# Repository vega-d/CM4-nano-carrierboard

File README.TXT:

These files have been created in prerelease version 6 of KiCAD. If Version 6 isn't released yet then to use them you will need to download a nightly build of KiCAD. NB Nightly builds my have issues so please check the issue tracker. 

Some of the 3d models need to be downloaded form the following places and put into the CM4IO.3shapes directory some models are approximations.

https://datasheets.raspberrypi.org/cm4/CM4-step.zip
https://www.amphenol-icc.com/pci-express-1001878311200tlf.html
https://www.te.com/global-en/product-171826-4.html
https://www.molex.com/molex/products/part-detail/memory_card_socket/5033981892

The models provided in the 3dmodels directory are from various manufacturers including Diodes, Hirose, MTCONN,Toby, TRXCOM. Terms and conditions for the use of the models remain with the original manufacture.

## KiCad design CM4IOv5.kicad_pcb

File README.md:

# CM4-nano-carrierboard
 A simplified carrier board for RPI CM4 module featuring reduced footprint.

- Uses 5V barrel plug charger for power.
- Has one full size HDMI port.
- has 2 usb-2.0 ports.
- sd card support.
- built-in gigabit ethernet.

SIZE: 80mm x 90mm.

- grounded infill
- use kicad 5.99 or newer.

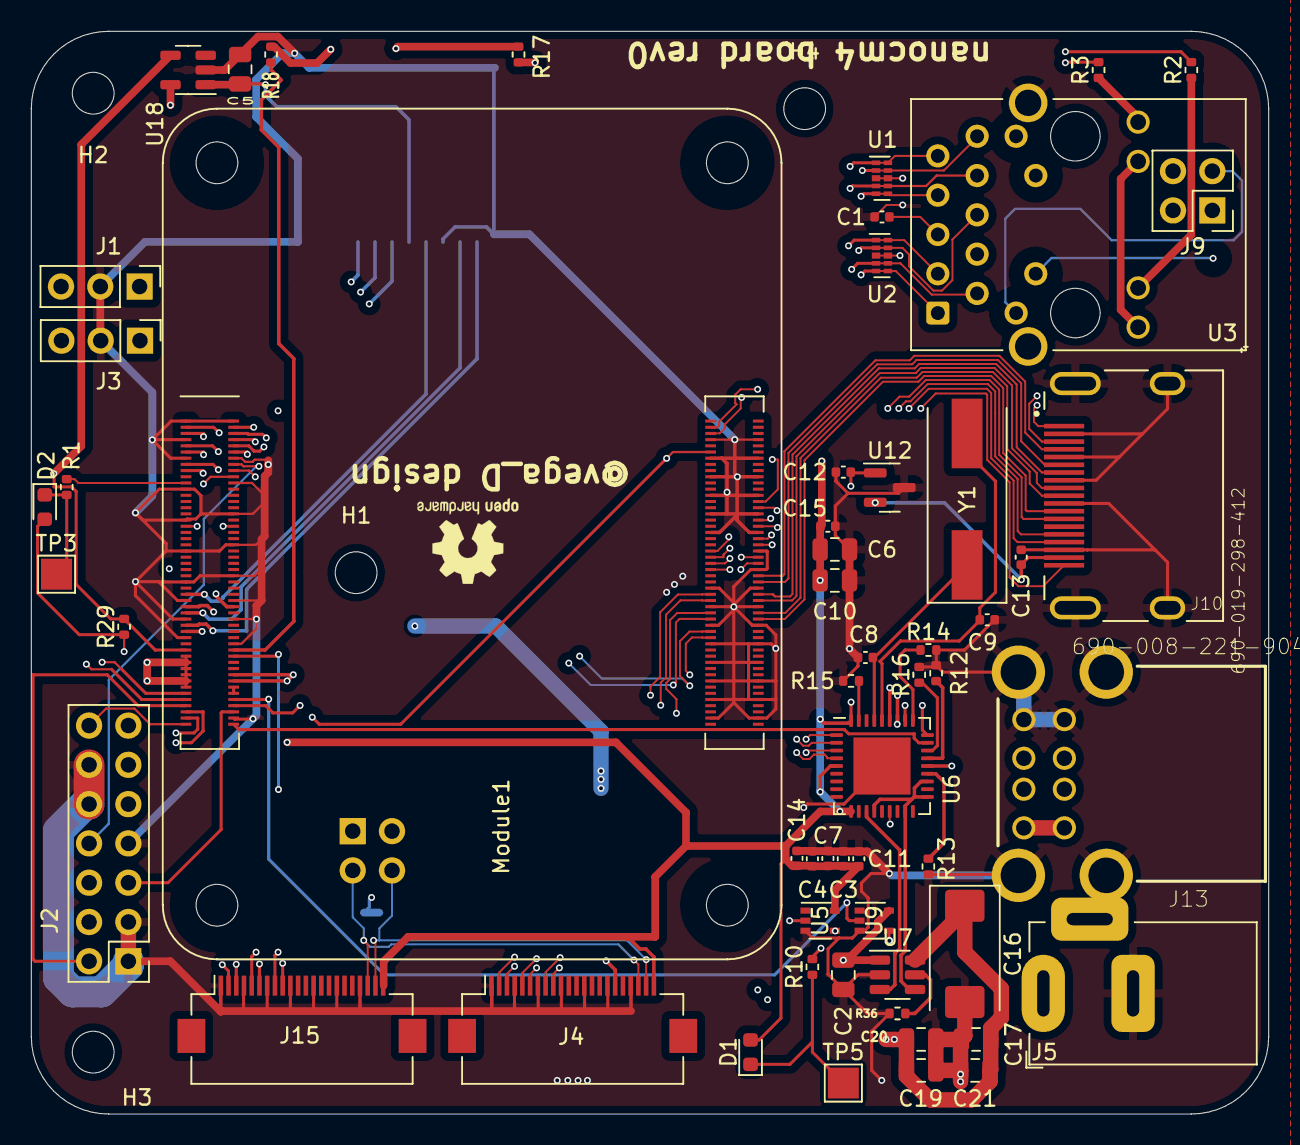
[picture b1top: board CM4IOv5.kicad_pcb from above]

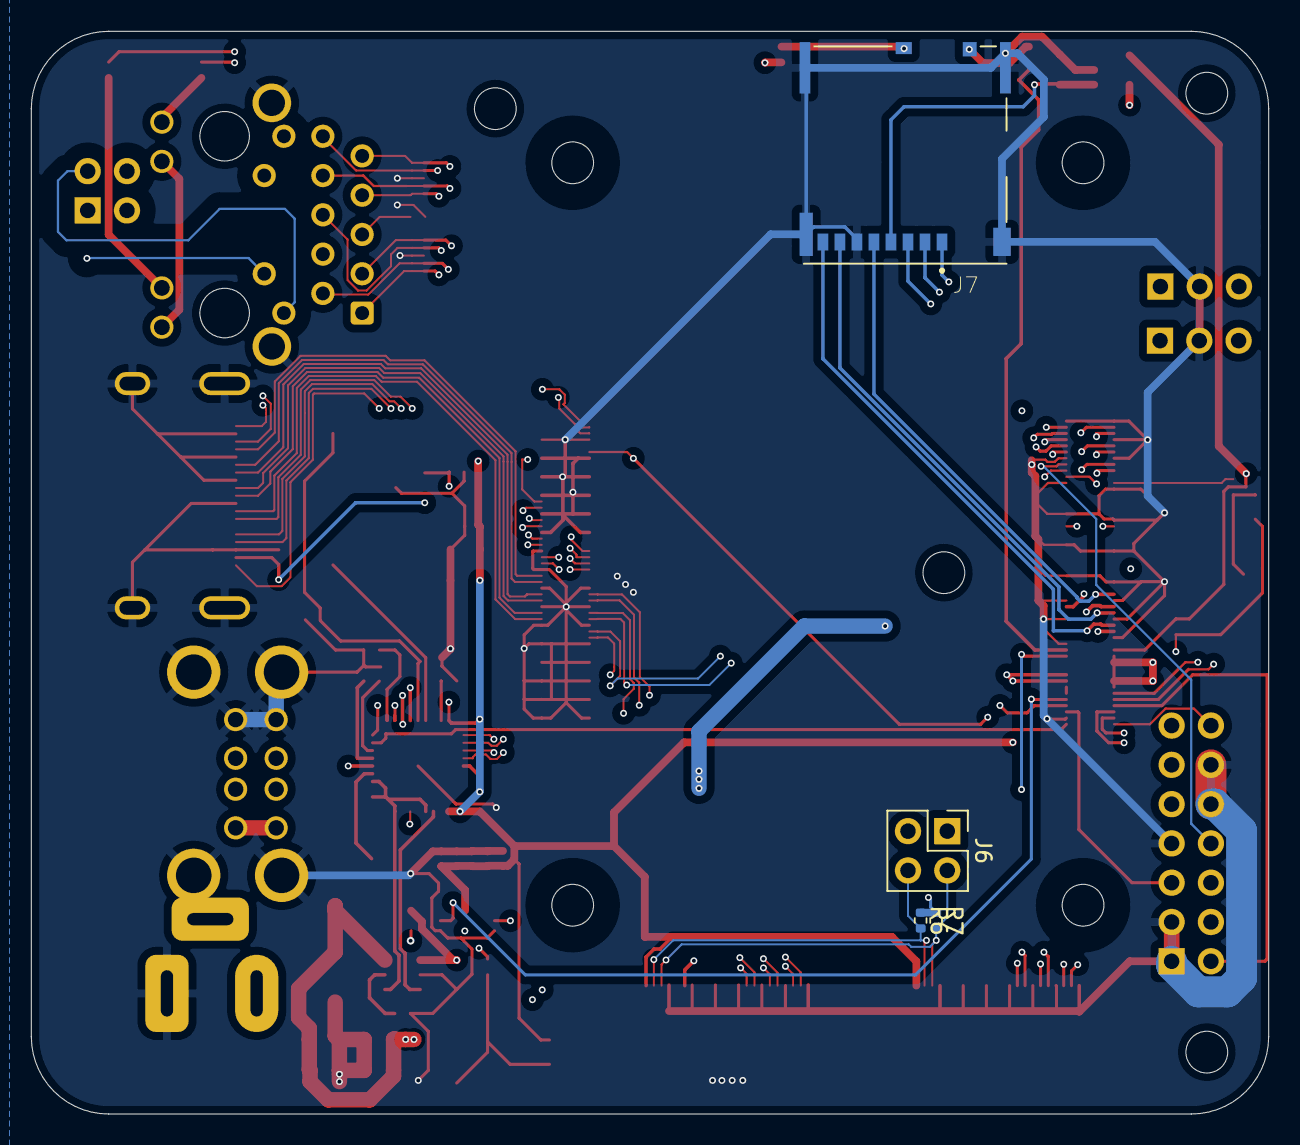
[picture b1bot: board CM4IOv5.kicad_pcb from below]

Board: 4 copper layers, 80.0 x 70.0 mm, 65 parts (4 on the bottom side), 98 nets.

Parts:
C1, C3, C4, C7, C11, C12, C13, C14, C15: 100n; C_0402_1005Metric
C2, C5, C6, C10, C17, C19, C20, C21: 10u; C_0805_2012Metric
C8, C9: 27pF; C_0402_1005Metric
C16: 100uF; CP_EIA-7343-31_Kemet-D
D1: LED Red; LED_0603_1608Metric
D2: LED Green; LED_0603_1608Metric
H1, H2, H3, H4: MountingHole; MountingHole_2.7mm_M2.5
J1, J3: Conn_01x03; PinHeader_1x03_P2.54mm_Vertical
J2: Conn_02x07_Odd_Even; PinHeader_2x07_P2.54mm_Vertical
J4, J15: Conn_01x22_Female; Hirose_FH12-22S-0.5SH_1x22-1MP_P0.50mm_Horizontal
J5: Barrel_Jack; BarrelJack_Horizontal
J6, J9: THD-02-R; PinHeader_2x02_P2.54mm_Vertical
J7: Micro_SD_Card_Det; SDCARD_MOLEX_503398-1892
J10: 690-019-298-412; EDAC 690-019-298-412
J13: 690-008-221-904; MOLEX_USB_67298-4090
Module1: ComputeModule4; Raspberry-Pi-4-Compute-Module
R1, R10: 1k; R_0402_1005Metric
R2, R3: 470R; R_0402_1005Metric
R6, R7: 2.2K 1%; R_0402_1005Metric
R12, R13, R14, R16: 36K 1%; R_0402_1005Metric
R15, R29: 12K 1%; R_0402_1005Metric
R17, R18: nf; R_0402_1005Metric
R36: 15K 1%; R_0402_1005Metric
TP3, TP5: TestPoint; TestPoint_Pad_2.0x2.0mm
U1, U2: TPD4EUSB30; USON-10_2.5x1.0mm_P0.5mm
U3: MagJack-A70-112-331N126; TRJG0926HENL
U5, U9: 74LVC1G07SE-7; SOT-353_SC-70-5
U6: USB2514B-I/M2; QFN-36-1EP_6x6mm_P0.5mm_EP3.7x3.7mm
U7: AP22653W6; SOT-23-6
U12: RT9742SNGV; SOT-23
U18: RT9742GGJ5; SOT-23-5
Y1: 24MHz; Crystal_SMD_HC49-SD

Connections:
+3.3v: C3.1, C4.1, C6.1, C7.1, C10.1, C11.1, C14.1, C15.1, D1.2 (A), D2.2 (A), J4.22, J15.22, Module1.84 (+3.3v_(Output)), Module1.86 (+3.3v_(Output)), R17.1, R29.1, U3.15 (LEDG_A), U3.17 (LEDY_A), U5.5 (VCC), U6.5 (VDDA33), U6.10 (VDDA33), U6.15 (VDD33), U6.23 (VDD33), U6.27 (VBUS_DET), U6.29 (VDDA33), U6.36 (VDDA33), U18.5 (IN)
/+5v: C2.1, C12.1, J5.1, Module1.77 (+5v_(Input)), Module1.79 (+5v_(Input)), Module1.81 (+5v_(Input)), Module1.83 (+5v_(Input)), Module1.85 (+5v_(Input)), Module1.87 (+5v_(Input)), U7.1 (IN), U9.5 (VCC), U12.1 (IN)
/CM4_GPIO ( Ethernet, GPIO, SDCARD)/+1.8v: Module1.88 (+1.8v_(Output)), Module1.90 (+1.8v_(Output))
/CM4_GPIO ( Ethernet, GPIO, SDCARD)/AIN0: J2.5, Module1.96 (AnalogIP0)
/CM4_GPIO ( Ethernet, GPIO, SDCARD)/AIN1: J2.6, Module1.94 (AnalogIP1)
/CM4_GPIO ( Ethernet, GPIO, SDCARD)/BT_nDis: J3.3, Module1.91 (BT_nDisable)
/CM4_GPIO ( Ethernet, GPIO, SDCARD)/EEPROM_nWP: J2.4, Module1.20 (EEPROM_nWP)
/CM4_GPIO ( Ethernet, GPIO, SDCARD)/ETH_LEDG: Module1.17 (Ethernet_nLED2(3.3v)), R2.2
/CM4_GPIO ( Ethernet, GPIO, SDCARD)/ETH_LEDY: Module1.15 (Ethernet_nLED3(3.3v)), R3.2
/CM4_GPIO ( Ethernet, GPIO, SDCARD)/GLOBAL_EN: J1.1, J2.14, Module1.99 (Global_EN)
/CM4_GPIO ( Ethernet, GPIO, SDCARD)/GPIO_VREF: Module1.78 (GPIO_VREF(1.8v/3.3v_Input)), R6.1, R7.1
/CM4_GPIO ( Ethernet, GPIO, SDCARD)/ID_SC: J6.1, Module1.35 (ID_SC)
/CM4_GPIO ( Ethernet, GPIO, SDCARD)/ID_SD: J6.3, Module1.36 (ID_SD)
/CM4_GPIO ( Ethernet, GPIO, SDCARD)/RUN_PG: J1.3, Module1.92 (RUN_PG), U9.2
/CM4_GPIO ( Ethernet, GPIO, SDCARD)/Reserved: Module1.76 (Reserved), R18.1
/CM4_GPIO ( Ethernet, GPIO, SDCARD)/SD_CLK: J7.5 (CLK), Module1.57 (SD_CLK)
/CM4_GPIO ( Ethernet, GPIO, SDCARD)/SD_CMD: J7.3 (CMD), Module1.62 (SD_CMD)
/CM4_GPIO ( Ethernet, GPIO, SDCARD)/SD_DAT0: J7.7 (DAT0), Module1.63 (SD_DAT0)
/CM4_GPIO ( Ethernet, GPIO, SDCARD)/SD_DAT1: J7.8 (DAT1), Module1.67 (SD_DAT1)
/CM4_GPIO ( Ethernet, GPIO, SDCARD)/SD_DAT2: J7.1 (DAT2), Module1.69 (SD_DAT2)
/CM4_GPIO ( Ethernet, GPIO, SDCARD)/SD_DAT3: J7.2 (DAT3/CD), Module1.61 (SD_DAT3)
/CM4_GPIO ( Ethernet, GPIO, SDCARD)/SD_PWR: C5.1, J7.4 (VDD), U18.1 (OUT)
/CM4_GPIO ( Ethernet, GPIO, SDCARD)/SD_PWR_ON: Module1.75 (SD_PWR_ON), R29.2, U18.4 (EN)
/CM4_GPIO ( Ethernet, GPIO, SDCARD)/SYNC_IN: J2.8, Module1.16 (Ethernet_SYNC_IN(1.8v))
/CM4_GPIO ( Ethernet, GPIO, SDCARD)/SYNC_OUT: J2.9, Module1.18 (Ethernet_SYNC_OUT(1.8v))
/CM4_GPIO ( Ethernet, GPIO, SDCARD)/TR0_TAP: J9.3, U3.11 (VC1)
/CM4_GPIO ( Ethernet, GPIO, SDCARD)/TR1_TAP: J9.1, U3.12 (VC2)
/CM4_GPIO ( Ethernet, GPIO, SDCARD)/TR2_TAP: J9.2, U3.13 (VC3)
/CM4_GPIO ( Ethernet, GPIO, SDCARD)/TR3_TAP: J9.4, U3.14 (VC4)
/CM4_GPIO ( Ethernet, GPIO, SDCARD)/TRD0_N: Module1.10 (Ethernet_Pair0_N), U2.4 (D2+), U2.7, U3.2 (TRD0-)
/CM4_GPIO ( Ethernet, GPIO, SDCARD)/TRD0_P: Module1.12 (Ethernet_Pair0_P), U2.5 (D2-), U2.6, U3.1 (TRD0+)
/CM4_GPIO ( Ethernet, GPIO, SDCARD)/TRD1_N: Module1.6 (Ethernet_Pair1_N), U2.2 (D1-), U2.9, U3.6 (TRD1-)
/CM4_GPIO ( Ethernet, GPIO, SDCARD)/TRD1_P: Module1.4 (Ethernet_Pair1_P), U2.1 (D1+), U2.10, U3.3 (TRD1+)
/CM4_GPIO ( Ethernet, GPIO, SDCARD)/TRD2_N: Module1.9 (Ethernet_Pair2_N), U1.4 (D2+), U1.7, U3.8 (TRD2-)
/CM4_GPIO ( Ethernet, GPIO, SDCARD)/TRD2_P: Module1.11 (Ethernet_Pair2_P), U1.5 (D2-), U1.6, U3.7 (TRD2+)
/CM4_GPIO ( Ethernet, GPIO, SDCARD)/TRD3_N: Module1.5 (Ethernet_Pair3_N), U1.2 (D1-), U1.9, U3.10 (TRD3-)
/CM4_GPIO ( Ethernet, GPIO, SDCARD)/TRD3_P: Module1.3 (Ethernet_Pair3_P), U1.1 (D1+), U1.10, U3.9 (TRD3+)
/CM4_GPIO ( Ethernet, GPIO, SDCARD)/TV_OUT: J2.11, Module1.111 (VDAC_COMP)
/CM4_GPIO ( Ethernet, GPIO, SDCARD)/WL_nDis: J3.1, Module1.89 (WL_nDisable)
/CM4_GPIO ( Ethernet, GPIO, SDCARD)/nPWR_LED: Module1.95 (nPI_LED_PWR), U5.2
/CM4_GPIO ( Ethernet, GPIO, SDCARD)/nRPIBOOT: J2.2, Module1.93 (nRPIBOOT)
/CM4_HighSpeed/CAM0_C_N: J4.8, Module1.140 (CAM0_C_N)
/CM4_HighSpeed/CAM0_C_P: J4.9, Module1.142 (CAM0_C_P)
/CM4_HighSpeed/CAM0_D0_N: J4.2, Module1.128 (CAM0_D0_N)
/CM4_HighSpeed/CAM0_D0_P: J4.3, Module1.130 (CAM0_D0_P)
/CM4_HighSpeed/CAM0_D1_N: J4.5, Module1.134 (CAM0_D1_N)
/CM4_HighSpeed/CAM0_D1_P: J4.6, Module1.136 (CAM0_D1_P)
/CM4_HighSpeed/CAM_GPIO: J4.17, Module1.97 (Camera_GPIO)
/CM4_HighSpeed/DSI0_C_N: J15.8, Module1.169 (DSI0_C_N)
/CM4_HighSpeed/DSI0_C_P: J15.9, Module1.171 (DSI0_C_P)
/CM4_HighSpeed/DSI0_D0_N: J15.2, Module1.157 (DSI0_D0_N)
/CM4_HighSpeed/DSI0_D0_P: J15.3, Module1.159 (DSI0_D0_P)
/CM4_HighSpeed/DSI0_D1_N: J15.5, Module1.163 (DSI0_D1_N)
/CM4_HighSpeed/DSI0_D1_P: J15.6, Module1.165 (DSI0_D1_P)
/CM4_HighSpeed/HDMI1_CEC: J10.13 (CEC), Module1.149 (HDMI1_CEC)
/CM4_HighSpeed/HDMI1_CK_N: J10.12 (CK-), Module1.166 (HDMI1_CLK_N)
/CM4_HighSpeed/HDMI1_CK_P: J10.10 (CK+), Module1.164 (HDMI1_CLK_P)
/CM4_HighSpeed/HDMI1_D0_N: J10.9 (D0-), Module1.160 (HDMI1_TX0_N)
/CM4_HighSpeed/HDMI1_D0_P: J10.7 (D0+), Module1.158 (HDMI1_TX0_P)
/CM4_HighSpeed/HDMI1_D1_N: J10.6 (D1-), Module1.154 (HDMI1_TX1_N)
/CM4_HighSpeed/HDMI1_D1_P: J10.4 (D1+), Module1.152 (HDMI1_TX1_P)
/CM4_HighSpeed/HDMI1_D2_N: J10.3 (D2-), Module1.148 (HDMI1_TX2_N)
/CM4_HighSpeed/HDMI1_D2_P: J10.1 (D2+), Module1.146 (HDMI1_TX2_P)
/CM4_HighSpeed/HDMI1_HOTPLUG: J10.19 (HPD/HEAC-), Module1.143 (HDMI1_HOTPLUG)
/CM4_HighSpeed/HDMI1_SCL: J10.15 (SCL), Module1.147 (HDMI1_SCL)
/CM4_HighSpeed/HDMI1_SDA: J10.16 (SDA), Module1.145 (HDMI1_SDA)
/CM4_HighSpeed/HDMI_5v: C13.1, J10.18 (+5V), U12.2 (OUT)
/CM4_HighSpeed/SCL1: J4.20, J6.2, J15.20, R7.2
/CM4_HighSpeed/SDA1: J4.21, J6.4, J15.21, R6.2
/USB2-HUB/HD1_N: J13.2 (D-`), U6.1 (USBDM_DN1/PRT_DIS_M1)
/USB2-HUB/HD1_P: J13.3 (D+`), U6.2 (USBDP_DN1/PRT_DIS_P1)
/USB2-HUB/HD2_N: J13.6 (D-), U6.3 (USBDM_DN2/PRT_DIS_M2)
/USB2-HUB/HD2_P: J13.7 (D+), U6.4 (USBDP_DN2/PRT_DIS_P2)
/USB2-HUB/PWR1: U6.12 (PRTPWR1/BC_EN1), U7.3 (EN)
/USB2-HUB/USBH_N: Module1.103 (USB2_N), U6.30 (USBDM_UP)
/USB2-HUB/USBH_P: Module1.105 (USB2_P), U6.31 (USBDP_UP)
/USB2-HUB/VBUS: C16.1, C17.1, C19.1, C20.1, C21.1, J13.1 (VBUS`), J13.5 (VBUS), U7.6 (OUT)
/USB2-HUB/nOCS1: U6.13 (OCS_N1), U6.17 (OCS_N2), U6.19 (OCS_N3), U6.21 (OCS_N4), U7.4 (nFault)
/nEXTRST: Module1.100 (nEXTRST), U6.26 (RESET_N)
GND: C1.2, C2.2, C3.2, C4.2, C5.2, C6.2, C7.2, C8.2, C9.2, C10.2, C11.2, C12.2, C13.2, C14.2, C15.2, C16.2, C17.2, C19.2, C20.2, C21.2, J1.2, J2.1, J2.3, J2.7, J2.10, J2.12, J3.2, J4.1, J4.4, J4.7, J4.10, J4.13, J4.16, J4.19, J5.2, J7.6 (VSS), J7.11 (SHIELD), J10.2 (D2S), J10.5 (D1S), J10.8 (D0S), J10.11 (CKS), J10.17 (GND), J10.SH1 (SH), J10.SH2 (SH), J10.SH3 (SH), J10.SH4 (SH), J13.4 (GND`), J13.8 (GND), J13.MT1, J13.MT2, J13.MT3, J13.MT4, J15.1, J15.4, J15.7, J15.10, J15.13, J15.16, J15.19, Module1.1 (GND), Module1.2 (GND), Module1.7 (GND), Module1.8 (GND), Module1.13 (GND), Module1.14 (GND), Module1.22 (GND), Module1.23 (GND), Module1.32 (GND), Module1.33 (GND), Module1.42 (GND), Module1.43 (GND), Module1.52 (GND), Module1.53 (GND), Module1.59 (GND), Module1.60 (GND), Module1.65 (GND), Module1.66 (GND), Module1.71 (GND), Module1.74 (GND), Module1.98 (GND), Module1.107 (GND), Module1.108 (GND), Module1.113 (GND), Module1.114 (GND), Module1.119 (GND), Module1.120 (GND), Module1.125 (GND), Module1.126 (GND), Module1.131 (GND), Module1.132 (GND), Module1.137 (GND), Module1.138 (GND), Module1.144 (GND), Module1.150 (GND), Module1.155 (GND), Module1.156 (GND), Module1.161 (GND), Module1.162 (GND), Module1.167 (GND), Module1.168 (GND), Module1.173 (GND), Module1.174 (GND), Module1.179 (GND), Module1.180 (GND), Module1.185 (GND), Module1.186 (GND), Module1.191 (GND), Module1.192 (GND), Module1.197 (GND), Module1.198 (GND), R12.2, R13.2, R14.2, R15.1, R16.2, R36.2, U1.3 (GND), U1.8 (GND), U2.3 (GND), U2.8 (GND), U3.19 (SHIELD), U3.20 (SHIELD), U5.3 (GND), U6.37 (VSS), U7.2 (GND), U9.3 (GND), U12.3 (GND), U18.2 (GND)
unnamed: C1.1, U3.4 (CT), U3.5 (CT)
unnamed: C8.1, U6.33 (XTALIN/CLKIN), Y1.1
unnamed: C9.1, U6.32 (XTALOUT), Y1.2
unnamed: D1.1 (K), R10.1, TP5.1
unnamed: D2.1 (K), R1.1, TP3.1
unnamed: J2.13, U9.4
unnamed: J7.9 (DET_B), R18.2
unnamed: J7.10 (DET_A), R17.2
unnamed: Module1.21 (PI_nLED_Activity), R1.2
unnamed: R2.1, U3.16 (LEDG_K)
unnamed: R3.1, U3.18 (LEDY_K)
unnamed: R10.2, U5.4
unnamed: R12.1, U6.24 (SCL/SMBCLK/CFG_SEL0)
unnamed: R13.1, U6.22 (SDA/SMBDATA/NON_REM1)
unnamed: R14.1, U6.28 (SUSP_IND/LOCAL_PWR/NON_REM0)
unnamed: R15.2, U6.35 (RBIAS)
unnamed: R16.1, U6.25 (HS_IND/CFG_SEL1)
unnamed: R36.1, U7.5 (ILIM)
